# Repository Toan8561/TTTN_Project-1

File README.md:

<<<<<<< HEAD
Thiết kế PCB sửa dụng phần mềm KiCAD 9.0
Doc:

    + EEVblog #859 - Bypass Capacitor Tutorial : https://youtu.be/BcJ6UdDx1vg?si=35-A0UtRlQvs7iyN

    + TVS diode:    How TVS Diodes work:    https://youtu.be/oKACLpBYhxU?si=mKHlLxu5FLY22Hed 
                    ESD Protection Basics:  https://youtu.be/MmG_m4xVNfQ?si=IdVZMXSdpt6oV1Al 

    + Usb type-c:   https://electronics.stackexchange.com/questions/588126/are-usb-type-c-pull-resistor-neccesary-on-cc-and-sbu-pins
                    https://electronics.stackexchange.com/questions/624732/connecting-usb-c-port-with-atmega32u4-questions

    + Crystal Ocilator: https://ecsxtal.com/crystal-and-oscillator-printed-circuit-board-design-considerations/

=======
Công việc:
    + Thiết một sever web cơ bản.
    + Tối ưu web để tiện để vào chip flash. 
    + Thiết kế nối với chip ethernet ENC28J60.
    + Thiết kế mô hình poe cho kết nối ethernet. chip PoE-PD (Power over Ethernet - Power Draw chip)
>>>>>>> Simulation

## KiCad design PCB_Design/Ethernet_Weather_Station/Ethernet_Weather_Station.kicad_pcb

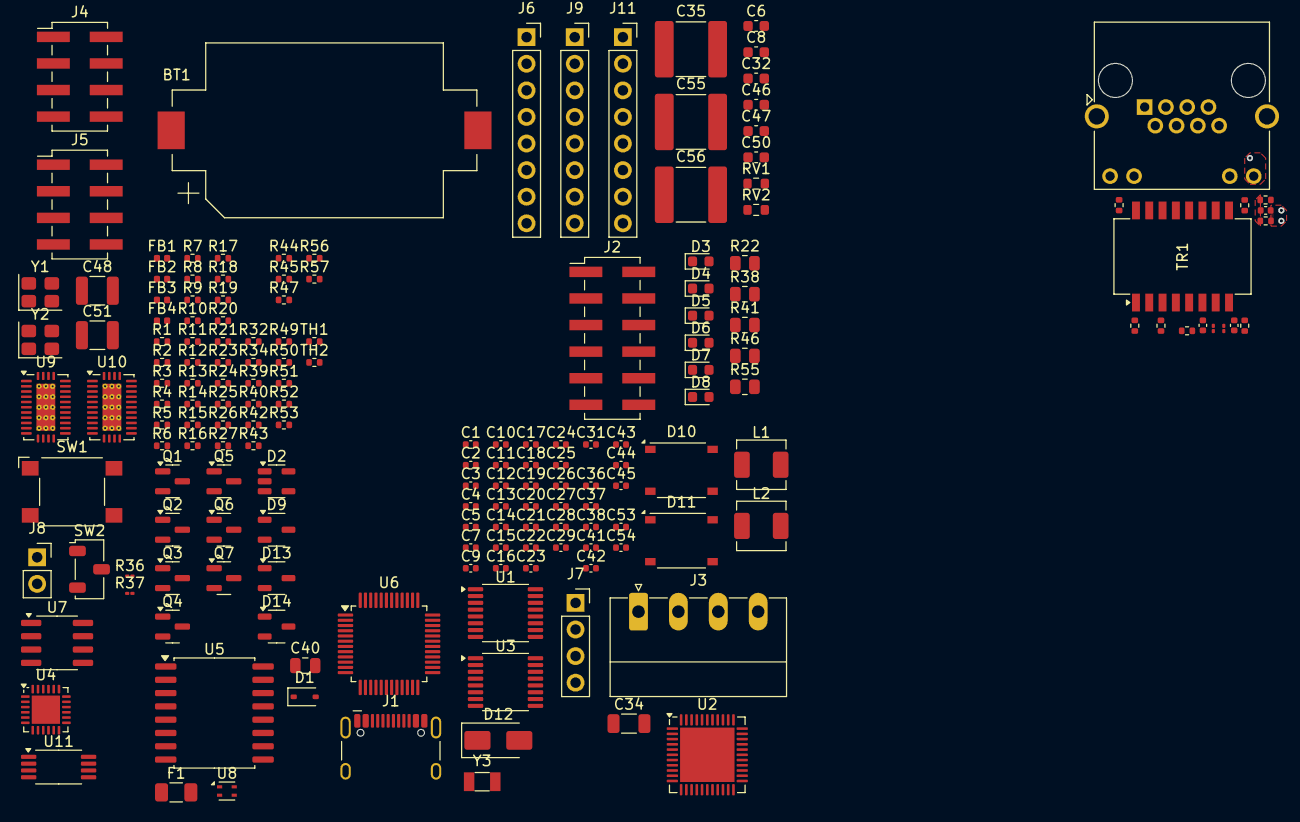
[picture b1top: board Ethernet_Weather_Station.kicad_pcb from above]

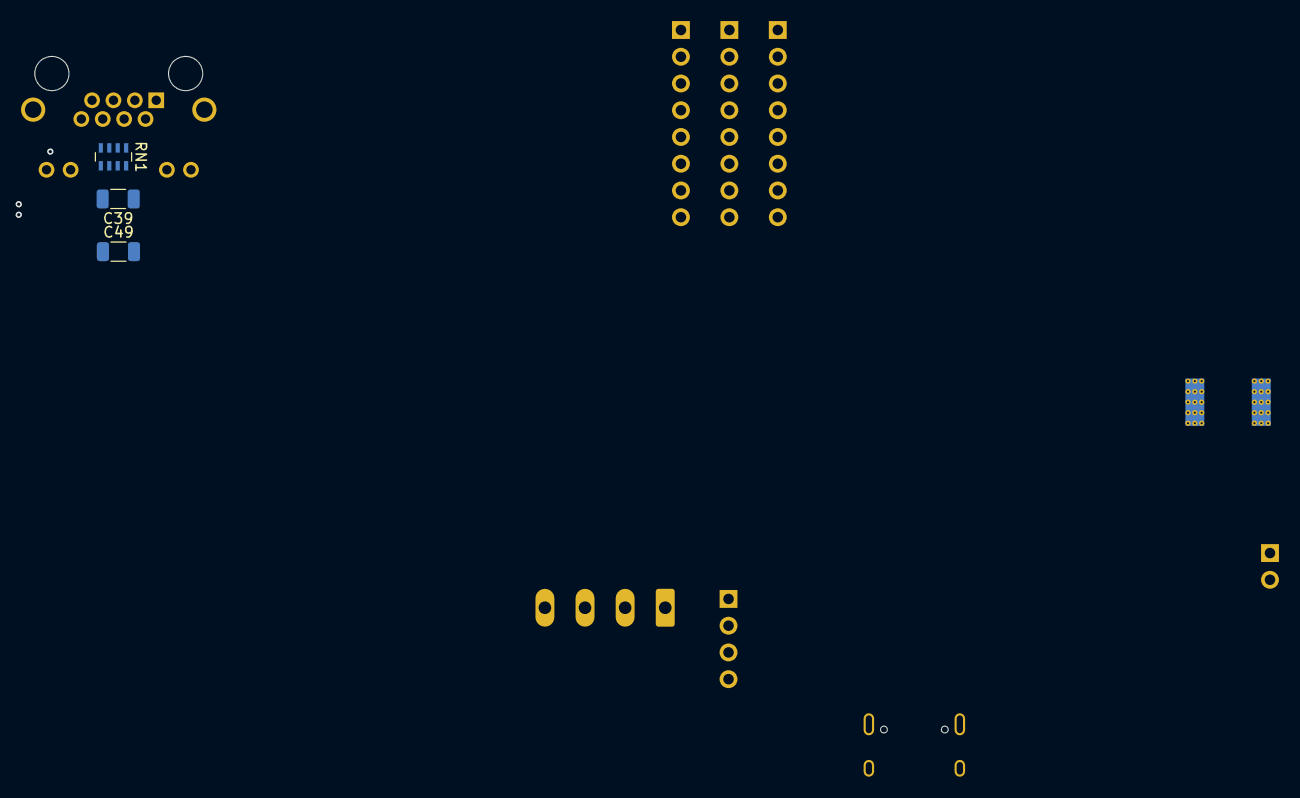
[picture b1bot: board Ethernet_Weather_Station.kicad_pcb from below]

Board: 4 copper layers, 177 parts (3 on the bottom side), 155 nets, no tracks yet.

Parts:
BT1: Battery_Cell; BatteryHolder_Keystone_1060_1x2032
C1, C5, C22, C28, C52: 10nF; C_0402_1005Metric
C2, C9, C10, C12, C13, C14, C15, C21, C23, C24, C26, C27, C29, C31: 0.1uF; C_0402_1005Metric
C3, C4, C17, C18: 22pF; C_0402_1005Metric
C6, C8, C32: 10uF; C_0603_1608Metric
C7, C11, C16, C19, C45: 1uF; C_0402_1005Metric
C20: 33pF; C_0402_1005Metric
C25: 4.7uF; C_0402_1005Metric
C30, C33: 6.8nF; C_0402_1005Metric
C34: 6.8uF; C_1206_3216Metric
C35: 6.8uF; C_2220_5750Metric
C36, C37, C38: 22nF; C_0402_1005Metric
C39: 4.7nF; C_1206_3216Metric
C40: 100nF; C_0805_2012Metric
C41, C42: 2.2uF; C_0402_1005Metric
C43, C44: 470nF; C_0402_1005Metric
C46: 1uF; C_0603_1608Metric
C47, C50: 22uF; C_0603_1608Metric
C48, C51: 22uF; C_1210_3225Metric
C49: 1nF 2kV; C_1206_3216Metric
C53, C54: 2.2pF; C_0402_1005Metric
C55, C56: 22uF; C_2220_5750Metric
D1: 1N4148WS; D_SOD-323
D2: ESDA5V3SC5; SOT-23-5
D3, D4, D5, D6, D7, D8: LED; LED_0603_1608Metric
D9, D13, D14: LGSOT05CLT1G; SOT-23-3
D10, D11: ABS2; Diode_Bridge_Diotec_ABS
D12: SMAJ58A; D_SMA
F1: 500mA Fuse; Fuse_1206_3216Metric
FB1, FB2, FB3, FB4: FerriteBead; L_0402_1005Metric
J1: USB_C_Receptacle_USB2.0_16P; USB_C_Receptacle_HCTL_HC-TYPE-C-16P-01A
J2: Conn_02x06; PinHeader_2x06_P2.54mm_Vertical_SMD
J3: RS485; PhoenixContact_MC_1,5_4-G-3.81_1x04_P3.81mm_Horizontal
J4, J5: Conn_02x04; PinHeader_2x04_P2.54mm_Vertical_SMD
J6: PE_PF; PinSocket_1x08_P2.54mm_Vertical
J7: JTAG; PinSocket_1x04_P2.54mm_Vertical
J8: PC; PinSocket_1x02_P2.54mm_Vertical
J9: PB0~7; PinSocket_1x08_P2.54mm_Vertical
J10: RJ45_LED_Shielded; RJ45_Amphenol_RJHSE538X
J11: PD0~7; PinSocket_1x08_P2.54mm_Vertical
L1: 1.2uH; L_APV_APH0420
L2: 1.5uH; L_APV_APH0420
Q1, Q2, Q3, Q4, Q5, Q6: BSN20; SOT-23
Q7: 2N7002; SOT-23
R1, R14, R15, R18, R25, R26: 4.7kΩ; R_0402_1005Metric
R2, R4, R5, R8, R9, R10, R11, R12, R13, R16, R17, R23, R24, R27, R32, R39, R42, R54: 10kΩ; R_0402_1005Metric
R3, R48: 50kΩ; R_0402_1005Metric
R6, R7: 22R; R_0402_1005Metric
R19, R20, R58, R59: 330Ω; R_0402_1005Metric
R21: 0Ω; R_0402_1005Metric
R22: 1MΩ; R_0805_2012Metric
R28, R29, R30, R31: 33Ω; R_0402_1005Metric
R33, R35, R36, R37: 51Ω; R_01005_0402Metric
R34: 12.4kΩ; R_0402_1005Metric
R38, R41: 143kΩ; R_0805_2012Metric
R40, R43: 17.4kΩ; R_0402_1005Metric
R44: 10Ω; R_0402_1005Metric
R45: 178kΩ; R_0402_1005Metric
R46: 24.9kΩ; R_0805_2012Metric
R47: 357Ω; R_0402_1005Metric
R49, R50: 75Ω; R_0402_1005Metric
R51, R53: 100kΩ; R_0402_1005Metric
R52: 43kΩ; R_0402_1005Metric
R55: 100kΩ; R_0805_2012Metric
R56, R57: 12kΩ; R_0402_1005Metric
RN1: 4x 75Ω; R_Array_Concave_4x0603
RV1, RV2: Varistors; R_0603_1608Metric
SW1: Button; SW_SPST_Omron_B3FS-100xP
SW2: SW_SPDT; Nidec_Copal_CAS-120A
TH1, TH2: 10K Thermistors; R_0402_1005Metric
TR1: PT61017PEL; Transformer_Ethernet_Bourns_PT61017PEL
U1, U3: ADS1220xPW; TSSOP-16_4.4x5mm_P0.65mm
U2: ATmega32U4-M; QFN-44-1EP_7x7mm_P0.5mm_EP5.2x5.2mm
U4: AW9523B; QFN-24-1EP_4x4mm_P0.5mm_EP2.7x2.7mm
U5: ADM2483xRW; SOIC-16W_7.5x10.3mm_P1.27mm
U6: W5500; LQFP-48_7x7mm_P0.5mm
U7: DS1302Z+; SOIC-8_3.9x4.9mm_P1.27mm
U8: SHT4x; Sensirion_DFN-4_1.5x1.5mm_P0.8mm_SHT4x_NoCentralPad
U9, U10: LM76002; Texas_RNP0030B_WQFN-30-1EP_4x6mm_P0.5mm_EP1.8x4.5mm_Thermal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
U11: TPS2375-1; TSSOP-8_4.4x3mm_P0.65mm
Y1: 16MHz; Crystal_SMD_3225-4Pin_3.2x2.5mm
Y2: Crystal; Crystal_SMD_3225-4Pin_3.2x2.5mm
Y3: 32.768kHz; Crystal_SMD_3215-2Pin_3.2x1.5mm

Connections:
+3.3V: C6.1, C7.1, C9.1, C10.1, C12.1, C19.2, C31.2, C45.1, C47.1, C50.1, C53.1, D1.1 (K), D3.2 (A), D4.2 (A), D5.2 (A), D6.2 (A), D7.2 (A), D8.2 (A), D13.1 (K), D13.2 (K), FB1.1, FB2.1, FB3.1, FB4.1, J4.8, J10.10, J10.12, L1.2, Q1.1 (G), Q2.1 (G), Q3.1 (G), Q4.1 (G), Q5.1 (G), Q6.1 (G), R1.1, R4.1, R8.2, R9.2, R14.2, R15.1, R16.1, R17.1, R18.2, R25.1, R27.1, R32.1, R49.2, R51.1, U1.13 (DVDD), U2.14 (VCC), U2.34 (VCC), U3.13 (DVDD), U4.21 (VCC), U5.1 (VDD1), U6.28 (VDD), U7.1 (VCC2), U8.3 (VDD), U9.9 (BIAS)
+3.3VA: C21.1, C23.1, C24.1, C26.1, C27.1, C29.1, C32.1, FB4.2, R36.2, R37.2, R44.2, U6.4 (AVDD), U6.8 (AVDD), U6.11 (AVDD), U6.15 (AVDD), U6.17 (AVDD), U6.21 (AVDD)
+5V: C46.1, C48.1, C51.1, C54.1, D14.1 (K), D14.2 (K), J4.1, L2.2, R10.1, R11.1, R12.1, R13.1, R23.1, R24.1, R50.2, R53.1, U10.9 (BIAS)
/#ADS1220_CS-1: U3.2 (~CS), U4.1 (P1_0)
/#ADS1220_CS-2: U1.2 (~CS), U4.2 (P1_1)
/#ADS1220_DRDY-1: R15.2, U3.14 (~DRDY), U4.3 (P1_2)
/#ADS1220_DRDY-2: R1.2, U1.14 (~DRDY), U4.4 (P1_3)
/#REST: D1.2 (A), R4.2, SW1.2, U2.13 (~RESET)
/+5V-#SS: D2.4 (K), J5.4, Q3.3 (D), R12.2
/+5V-MISO: D2.1 (K), J5.1, Q2.2 (S), R10.2
/+5V-MOSI: D2.3 (K), J5.2, Q1.3 (D), R11.2
/+5V-SCK: D2.5 (K), J5.3, Q4.2 (S), R13.2
/+5V-SCL: J4.4, Q6.3 (D), R23.2
/+5V-SDA: J4.2, Q5.2 (S), R24.2
/ACTLED: R59.2, U6.27 (ACTLED)
/AREF: C2.1, C5.1, U2.42 (AREF)
/DUPLED: R20.1, U6.26 (DUPLED)
/LINKLED: R58.2, U6.25 (LINKLED)
/NET_#INT: U4.8 (P0_3), U6.36 (~INT)
/NET_#RST: U4.10 (P0_4), U6.37 (~RST)
/NET_#SCS: U4.7 (P0_2), U6.32 (~SCS)
/NET_PMODE0: U4.11 (P0_5), U6.45 (PMODE0)
/NET_PMODE1: U4.12 (P0_6), U6.44 (PMODE1)
/NET_PMODE2: U4.13 (P0_7), U6.43 (PMODE2)
/PB0/#SS: J5.5, J9.1, Q3.2 (S), R16.2, U2.8 (PB0)
/PB1/SCK: J5.6, J9.2, Q4.3 (D), R17.2, U1.1 (SCLK), U2.9 (PB1), U3.1 (SCLK), U6.33 (SCLK), U7.7 (SCLK)
/PB2/MOSI: J5.7, J9.3, Q1.2 (S), R8.1, R26.1, U1.16 (DIN), U2.10 (PB2), U3.16 (DIN), U6.35 (MOSI)
/PB3/MISO: J5.8, J9.4, Q2.3 (D), R9.1, R26.2, U1.15 (DOUT/~DRDY), U2.11 (PB3), U3.15 (DOUT/~DRDY), U6.34 (MISO), U7.6 (I/O)
/PB4: J9.5, U2.28 (PB4)
/PB5: J9.6, U2.29 (PB5)
/PB6: J9.7, U2.30 (PB6)
/PB7/#RST: J9.8, U2.12 (PB7)
/PC6: J8.1, U2.31 (PC6)
/PC7/CLKO: J8.2, U2.32 (PC7)
/PD0/SCL: D9.2 (K), J4.5, J11.1, Q6.2 (S), R32.2, U2.18 (PD0), U4.19 (SCL), U8.2 (SCL)
/PD1/SDA: D9.1 (K), J4.7, J11.2, Q5.3 (D), R27.2, U2.19 (PD1), U4.20 (SDA), U8.1 (SDA)
/PD2/RX: J11.3, U2.20 (PD2), U5.6 (TxD)
/PD3/TX: J11.4, U2.21 (PD3), U5.3 (RxD)
/PD4: J11.5, U2.25 (PD4)
/PD5/#CTS: J11.6, U2.22 (PD5)
/PD6: J11.7, U2.26 (PD6)
/PD7: J11.8, U2.27 (PD7)
/PE2: J6.1, SW2.3 (A)
/PE2/#HWB: SW2.2 (B), U2.33 (~HWB/PE2)
/PE6: J6.2, U2.1 (PE6)
/PF0: J6.3, U2.41 (PF0)
/PF1: J6.4, U2.40 (PF1)
/PF4/TCK: J6.5, J7.1, U2.39 (PF4)
/PF5/TMS: J6.6, J7.2, U2.38 (PF5)
/PF6/TDO: J6.7, J7.3, U2.37 (PF6)
/PF7/TD1: J6.8, J7.4, U2.36 (PF7)
/PGOOD_3V3: R49.1, U9.16 (PGOOD)
/PGOOD_5V: R50.1, U10.16 (PGOOD)
/PoE_OUT: C34.1, C35.1, C40.1, C55.1, C56.1, D10.1 (+), D11.1 (+), D12.1 (A1), R38.1, R41.1, R46.1, R55.1, U9.20 (PVIN), U9.21 (PVIN), U9.22 (PVIN), U10.20 (PVIN), U10.21 (PVIN), U10.22 (PVIN), U11.8 (VDD)
/RDT: D10.3, RN1.8 (R1.2), TR1.10 (C_RX)
/RJ45_45: D11.4, J10.4, J10.5, RN1.6 (R3.2)
/RJ45_78: D11.3, J10.7, J10.8, RN1.5 (R4.2)
/RS485_RW: U4.6 (P0_1), U5.4 (~RE), U5.5 (DE)
/RTC_CE: Q7.1 (G), U4.5 (P0_0)
/RXN: C33.2, TR1.8 (RD-)
/RXP: C30.2, TR1.6 (RD+)
/SPDLED: R19.1, U6.24 (SPDLED)
/TCT: D10.4, RN1.7 (R2.2), TR1.15 (C_TX)
/TXN: R28.2, R37.1, TR1.3 (TD-)
/TXP: R29.2, R36.1, TR1.1 (TD+)
D+: R6.2, U2.4 (D+)
D-: R7.2, U2.3 (D-)
GND: BT1.2 (-), C1.2, C2.2, C3.1, C4.1, C5.2, C6.2, C7.2, C8.2, C9.2, C10.2, C11.2, C12.2, C13.2, C14.2, C15.2, C16.2, C17.1, C18.1, C19.1, C20.2, C21.2, C22.2, C23.2, C24.2, C25.2, C26.2, C27.2, C28.2, C29.2, C31.1, C32.2, C34.2, C35.2, C36.2, C37.2, C38.2, C41.2, C42.2, C45.2, C46.2, C47.2, C48.2, C49.1, C50.2, C51.2, C52.2, C55.2, C56.2, D2.2 (A), D9.3 (A), D13.3 (A), D14.3 (A), J1.A1 (GND), J1.A12 (GND), J1.B1 (GND), J1.B12 (GND), J4.3, J4.6, Q7.2 (S), R3.2, R5.2, R34.2, R39.1, R40.1, R42.1, R43.1, R48.2, R52.2, R57.1, RV1.2, RV2.2, SW1.1, TH1.2, TH2.2, U1.3 (CLK), U1.4 (DGND), U1.5 (AVSS), U2.5 (UGND), U2.15 (GND), U2.23 (GND), U2.35 (GND), U2.43 (GND), U2.45 (GND), U3.3 (CLK), U3.4 (DGND), U3.5 (AVSS), U4.9 (GND), U4.25 (GND), U5.2 (GND1), U5.8 (GND1), U6.3 (AGND), U6.9 (AGND), U6.14 (AGND), U6.16 (AGND), U6.19 (AGND), U6.29 (GND), U6.48 (AGND), U7.4 (GND), U8.4 (VSS), U9.13 (AGND), U9.14 (AGND), U9.15 (AGND), U9.17 (SYNC/MODE), U9.19 (NC_{GND}), U9.24 (PGND), U9.25 (PGND), U9.26 (PGND), U9.27 (NC_{GND}), U9.28 (NC_{GND}), U9.29 (NC_{GND}), U9.30 (NC_{GND}), U9.31 (AGND), U10.13 (AGND), U10.14 (AGND), U10.15 (AGND), U10.17 (SYNC/MODE), U10.19 (NC_{GND}), U10.24 (PGND), U10.25 (PGND), U10.26 (PGND), U10.27 (NC_{GND}), U10.28 (NC_{GND}), U10.29 (NC_{GND}), U10.30 (NC_{GND}), U10.31 (AGND), U11.5 (RTN), Y1.2, Y1.4, Y2.2, Y2.4
GNDPWR: C39.1, C49.2
unnamed: BT1.1 (+), U7.8 (VCC1)
unnamed: C1.1, R2.2, R3.1
unnamed: C13.1, C14.1, C15.1, C16.1, FB2.2, U2.24 (AVCC), U2.44 (AVCC)
unnamed: C18.2, R21.1, Y2.1
unnamed: C30.1, R31.2, R33.1
unnamed: C33.1, R30.2, R35.1
unnamed: C43.2, L1.1, U9.1 (SW), U9.2 (SW), U9.3 (SW), U9.4 (SW), U9.5 (SW)
unnamed: C44.2, L2.1, U10.1 (SW), U10.2 (SW), U10.3 (SW), U10.4 (SW), U10.5 (SW)
unnamed: C52.1, R48.1, R54.2
unnamed: D3.1 (K), U4.14 (P1_4)
unnamed: D4.1 (K), U4.15 (P1_5)
unnamed: D5.1 (K), U4.16 (P1_6)
unnamed: D6.1 (K), U4.17 (P1_7)
unnamed: D7.1 (K), R19.2
unnamed: D8.1 (K), R20.2
unnamed: C40.2, D10.2 (-), D11.2 (-), D12.2 (A2), R45.2, R47.2, U11.4 (VSS)
unnamed: F1.1, J1.A4 (VBUS), J1.A9 (VBUS), J1.B4 (VBUS), J1.B9 (VBUS)
unnamed: J1.A5 (CC1), TH2.1
unnamed: J1.B5 (CC2), TH1.1
unnamed: J1.A6 (D+), J1.B6 (D+), R6.1, RV2.1
unnamed: J1.A7 (D-), J1.B7 (D-), R7.1, RV1.1
unnamed: J1.S1 (SHIELD), R2.1
unnamed: J2.1, U1.9 (REFP0)
unnamed: J2.2, U1.11 (AIN0/REFP1)
unnamed: J2.3, U1.10 (AIN1)
unnamed: J2.4, U1.7 (AIN2)
unnamed: J2.5, U1.6 (AIN3/REFN1)
unnamed: J2.6, U1.8 (REFN0)
unnamed: J2.7, U3.8 (REFN0)
unnamed: J2.8, U3.6 (AIN3/REFN1)
unnamed: J2.9, U3.7 (AIN2)
unnamed: J2.10, U3.10 (AIN1)
unnamed: J2.11, U3.11 (AIN0/REFP1)
unnamed: J2.12, U3.9 (REFP0)
unnamed: J3.1, U5.16 (VDD2)
unnamed: J3.2, U5.12 (A)
unnamed: J3.3, U5.13 (B)
unnamed: J3.4, U5.9 (GND2), U5.15 (GND2)
unnamed: J10.9, R59.1
unnamed: J10.11, R58.1
unnamed: J10.SH, R54.1
unnamed: C20.1, Q7.3 (D), R25.2, U7.5 (CE)
unnamed: R56.2, R57.2
unnamed: C39.2, RN1.1 (R1.1), RN1.2 (R2.1), RN1.3 (R3.1), RN1.4 (R4.1)
unnamed: R5.1, SW2.1 (C)
unnamed: C28.1, R33.2, R35.2, TR1.7 (C_RD)
unnamed: C38.1, R44.1, TR1.2 (C_TD)
unnamed: J10.3, TR1.11 (RX+)
unnamed: J10.6, TR1.9 (RX-)
unnamed: J10.1, TR1.16 (TX+)
unnamed: J10.2, TR1.14 (TX-)
unnamed: FB1.2, U1.12 (AVDD)
unnamed: C11.1, U2.6 (UCAP)
unnamed: C3.2, U2.17 (XTAL1), Y1.3
unnamed: C4.2, U2.16 (XTAL2), Y1.1
unnamed: FB3.2, U3.12 (AVDD)
unnamed: R18.1, U4.18 (AD0)
unnamed: R14.1, U4.24 (AD1)
unnamed: C22.1, U6.22 (1V2O)
unnamed: R34.1, U6.10 (EXRES1)
unnamed: R30.1, U6.5 (RXN)
unnamed: R31.1, U6.6 (RXP)
unnamed: C25.1, U6.20 (TOCAP)
unnamed: R28.1, U6.1 (TXN)
unnamed: R29.1, U6.2 (TXP)
unnamed: C17.2, R22.1, U6.30 (XI/CLKIN), Y2.3
unnamed: R21.2, R22.2, U6.31 (XO)
unnamed: U7.2 (X1), Y3.1
unnamed: U7.3 (X2), Y3.2
unnamed: C43.1, U9.6 (BOOT)
unnamed: R38.2, R39.2, U9.18 (EN)
unnamed: C53.2, R51.2, R52.1, U9.12 (FB)
unnamed: R40.2, U9.10 (RT)
unnamed: C36.1, U9.11 (SS/TRK)
unnamed: C41.1, U9.8 (VCC)
unnamed: C44.1, U10.6 (BOOT)
unnamed: R41.2, R42.2, U10.18 (EN)
unnamed: C54.2, R53.2, R56.1, U10.12 (FB)
unnamed: R43.2, U10.10 (RT)
unnamed: C37.1, U10.11 (SS/TRK)
unnamed: C42.1, U10.8 (VCC)
unnamed: R47.1, U11.2 (CLASS)
unnamed: R46.2, U11.3 (DET)
unnamed: R45.1, U11.1 (ILIM)
unnamed: R55.2, U11.6 (PG)
VBUS: C8.1, F1.2, U2.2 (UVCC), U2.7 (VBUS)

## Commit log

2025-06-02 Make project
2025-06-02 change crystal speed
2025-06-02 Phan cong viec
2025-06-02 nhiet do - do am
2025-06-02 add simulation
2025-06-03 data sheet
2025-06-03 DHT11 datasheet
2025-06-03 Interfacing of DHT11
2025-06-03 thêm tính năng và doc cho module ethernet
2025-06-04 Thu vien DHT11
2025-06-06 Add LM393 based sensor, capacitive sensor, docs, simulation
2025-06-07 modified: README.md
2025-06-10 add funtion in ReadMe
2025-06-10 Add One-Wire simulation
2025-06-10 DHT11
2025-06-10 Change funtion
2025-06-10 SD card
2025-06-12 Ket noi ethernet
2025-06-12 Ket noi
2025-06-13 modified: README.md "Change project subject" new file: Smart_Graden modified: Src_Sim/Demo/Demo.pdsprj.ADMIN-PC.Admin.workspace new file: Weather_Station.md
2025-06-13 " Clean up branch "
2025-06-13 " Make Ethernet_SDcard branch "
2025-06-13 new file: Doc/Atmel-7766-8-bit-AVR-ATmega16U4-32U4_Datasheet.pdf "add atmega32u4 date sheet" new file: Doc/ENC28J60 Data Sheet.pdf "add ENC28J60 date sheet" modified: README.md "Add not and work"
2025-06-14 new file: Doc/Atmel-7766-8-bit-AVR-ATmega16U4-32U4_Datasheet.pdf "Atmega32U4 data sheet" new file: Doc/SHT4x_Temperature_Humidity_Sensor.pdf "SHT4x sensor data sheet" new file: Doc/Sensirion_Datashee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
2025-06-15 Make new branch
2025-06-15 modified: Src_Sim/Usb_sensor/platformio.ini " Set chip to internal clock "
2025-06-15 modified: Src_Sim/Ethernet_SDcard/platformio.ini "switch MCU to internal clock 8MHz"
2025-06-15 new file: Report/Toan_weekly_report_June_15.docx "Add weekly report"
2025-06-17 modified: PCB_Design/Ethernet_Weather_Station/Ethernet_Weather_Station.kicad_sch "Add based compoment" modified: README.md "Add needed document"
2025-06-17 update gitignore
2025-06-17 clean up file
2025-06-17 ignore back-up file
2025-06-17 clean up ignore file
2025-06-17 update git ignore
2025-06-17 Clean up ignore files
2025-06-19 Add version 2 of simulation, ATmega32U4
2025-06-19 "Add usb and sensor"
2025-06-22 add report template
2025-06-23 "add Simulation libraries"
2025-06-24 Source code
2025-06-26 modified: Report/Bao_Cao_TT_Ver_100.docx "Making finnal report" new file: Report/Weekly report/Toan_weekly_report_June_22.docx "Add Weekly report"
2025-06-27 "make zip file"
2025-06-27 modified: TTTN_Project-1.code-workspace "update workspace"
2025-06-27 clean up simulation file
2025-06-28 add componet tp schematic
2025-06-28 source
2025-06-29 Finally schematic
2025-06-29 modified: Smart_Graden.md "thay đổi phân công"
2025-07-01 "add simulation code"
2025-07-03 update PCB design
2025-07-04 add simulation picture
2025-07-04 add daily report
2025-07-04 " add EDC protecion"
2025-07-05 modified: Src_Sim/Soil_Moisture_Sensor/platformio.ini "Fix merge error"
